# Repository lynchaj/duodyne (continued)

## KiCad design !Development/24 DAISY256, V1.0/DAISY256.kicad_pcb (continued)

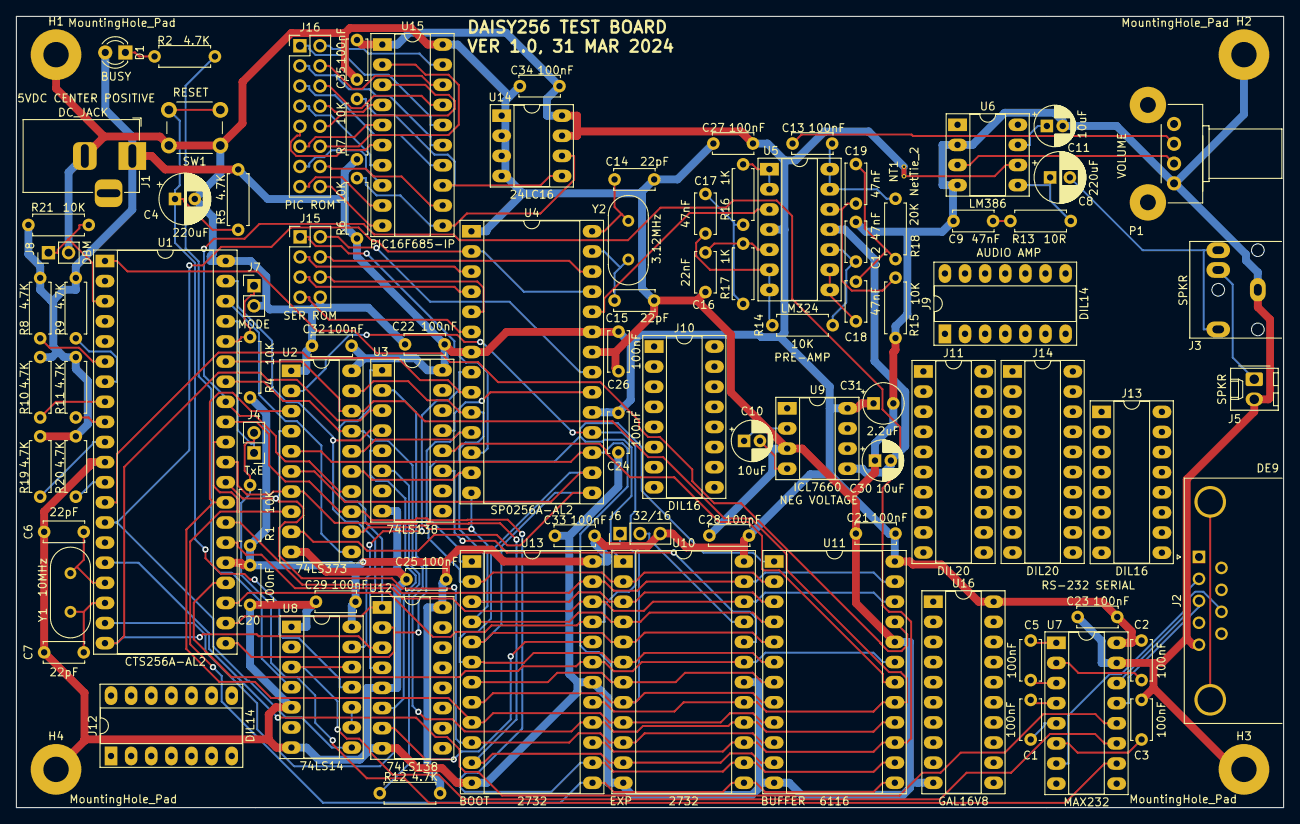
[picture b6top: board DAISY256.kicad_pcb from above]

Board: 2 copper layers, 160.0 x 99.9 mm, 97 parts (0 on the bottom side), 113 nets.

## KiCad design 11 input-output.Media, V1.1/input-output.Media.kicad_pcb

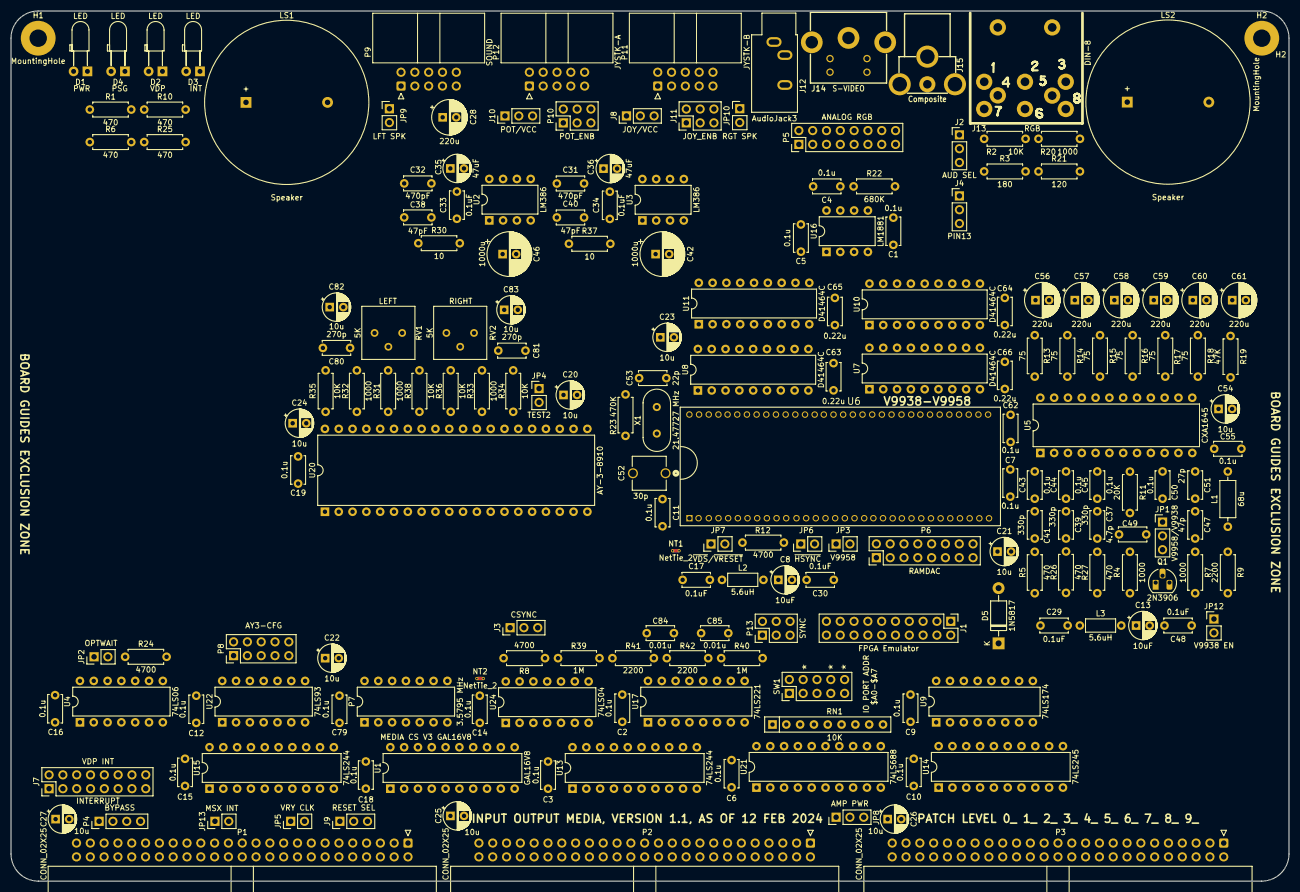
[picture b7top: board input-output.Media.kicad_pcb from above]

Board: 2 copper layers, 235.0 x 160.0 mm, 191 parts (0 on the bottom side), 242 nets, no tracks yet.

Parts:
C1, C2, C3, C4, C5, C6, C7, C9, C10, C11, C12, C14, C15, C16, C18, C19, C43, C44, C45, C50, C55, C62, C79: 0.1u; C_Disc_D5.0mm_W2.5mm_P5.00mm
C8, C13: 10uF; CP_Radial_D5.0mm_P2.50mm
C17, C29, C30, C33, C34, C48: 0.1uF; C_Disc_D5.0mm_W2.5mm_P5.00mm
C20, C21, C22, C23, C24, C25, C26, C27, C54, C82, C83: 10u; CP_Radial_D5.0mm_P2.50mm
C28, C56, C57, C58, C59, C60, C61: 220u; CP_Radial_D6.3mm_P2.50mm
C31, C32: 470pF; C_Disc_D5.0mm_W2.5mm_P5.00mm
C35, C36: 47uF; CP_Radial_D5.0mm_P2.50mm
C37, C39, C41: 330p; C_Disc_D5.0mm_W2.5mm_P5.00mm
C38, C40: 47pF; C_Disc_D5.0mm_W2.5mm_P5.00mm
C42, C46: 1000u; CP_Radial_D8.0mm_P2.50mm
C47: 47p; C_Disc_D5.0mm_W2.5mm_P5.00mm
C49: 4.7p; C_Disc_D5.0mm_W2.5mm_P5.00mm
C51: 27p; C_Disc_D5.0mm_W2.5mm_P5.00mm
C52: 30p; CAP_TZ03R300E169B00_MUR
C53: 22p; C_Disc_D5.0mm_W2.5mm_P5.00mm
C63, C64, C65, C66: 0.22u; C_Disc_D5.0mm_W2.5mm_P5.00mm
C80, C81: 270p; C_Disc_D5.0mm_W2.5mm_P5.00mm
C84, C85: 0.01u; C_Disc_D5.0mm_W2.5mm_P5.00mm
D1, D2, D3, D4: LED; LED_D3.0mm_Horizontal_O3.81mm_Z2.0mm
D5: 1N5817; D_DO-41_SOD81_P10.16mm_Horizontal
H1, H2: MountingHole; MountingHole_3.2mm_M3_Pad
J1: FPGA Emulator; PinHeader_2x10_P2.54mm_Vertical
J2: AUD SEL; PinHeader_1x03_P2.54mm_Vertical
J3: CSYNC; PinHeader_1x03_P2.54mm_Vertical
J4: PIN13; PinHeader_1x03_P2.54mm_Vertical
J7: INTERRUPT; PinHeader_2x08_P2.54mm_Vertical
J8: JOY/VCC; PinHeader_1x03_P2.54mm_Vertical
J9: RESET SEL; PinHeader_1x03_P2.54mm_Vertical
J10: POT/VCC; PinHeader_1x03_P2.54mm_Vertical
J11: JOY_ENB; PinHeader_2x03_P2.54mm_Vertical
J12: AudioJack3; Jack_3.5mm_CUI_SJ1-3533NG_Horizontal
J13: RGB; AV_CON_DIN8
J14: S-VIDEO; Conn_Mini_DIN_4pin
J15: Composite; Conn_RCA_Right
JP1: V9958/V9938; PinHeader_1x03_P2.54mm_Vertical
JP2: OPTWAIT; PinHeader_1x02_P2.54mm_Vertical
JP3: V9958; PinHeader_1x02_P2.54mm_Vertical
JP4: TEST2; PinHeader_1x02_P2.54mm_Vertical
JP5: VRY CLK; PinHeader_1x02_P2.54mm_Vertical
JP6: ~{HSYNC}; PinHeader_1x02_P2.54mm_Vertical
JP7: ~{VDS}/~{VRESET}; PinHeader_1x02_P2.54mm_Vertical
JP8: AMP PWR; PinHeader_1x03_P2.54mm_Vertical
JP9: LFT SPK; PinHeader_1x02_P2.54mm_Vertical
JP10: RGT SPK; PinHeader_1x02_P2.54mm_Vertical
JP12: V9938 EN; PinHeader_1x02_P2.54mm_Vertical
JP13: MSX INT; PinHeader_1x02_P2.54mm_Vertical
L1: 68u; L_Axial_L6.6mm_D2.7mm_P10.16mm_Horizontal_Vishay_IM-2
L2, L3: 5.6uH; L_Axial_L5.3mm_D2.2mm_P7.62mm_Horizontal_Vishay_IM-1
LS1, LS2: Speaker; Jameco PCB Speaker 30mm 135722
NT1, NT2: NetTie_2; NetTie-2_THT_Pad0.3mm
P1, P2, P3: CONN_02X25; IDC-Header_2x25_P2.54mm_Horizontal
P4: BYPASS; PinHeader_1x04_P2.54mm_Vertical
P5: ANALOG RGB; PinHeader_2x08_P2.54mm_Vertical
P6: RAMDAC; PinHeader_2x08_P2.54mm_Vertical
P7: 3.5795 MHz; DIP-14_W7.62mm
P8: AY3-CFG; PinHeader_2x05_P2.54mm_Vertical
P9: SOUND; IDC-Header_2x05_P2.54mm_Horizontal
P10: POT_ENB; PinHeader_2x03_P2.54mm_Vertical
P11: JYSTK-B; IDC-Header_2x05_P2.54mm_Horizontal
P12: JYSTK-A; IDC-Header_2x05_P2.54mm_Horizontal
P13: SYNC; PinHeader_2x03_P2.54mm_Vertical
Q1: 2N3906; TO-92_HandSolder
R1, R5, R6, R10, R25, R26, R27: 470; R_Axial_DIN0207_L6.3mm_D2.5mm_P7.62mm_Horizontal
R2, R34, R35, R36, R38: 10K; R_Axial_DIN0207_L6.3mm_D2.5mm_P7.62mm_Horizontal
R3: 180; R_Axial_DIN0207_L6.3mm_D2.5mm_P7.62mm_Horizontal
R4, R7, R20, R31, R32, R33: 1000; R_Axial_DIN0207_L6.3mm_D2.5mm_P7.62mm_Horizontal
R8, R12, R24: 4700; R_Axial_DIN0207_L6.3mm_D2.5mm_P7.62mm_Horizontal
R9, R41, R42: 2200; R_Axial_DIN0207_L6.3mm_D2.5mm_P7.62mm_Horizontal
R11: 20K; R_Axial_DIN0207_L6.3mm_D2.5mm_P7.62mm_Horizontal
R13, R14, R15, R16, R17, R18: 75; R_Axial_DIN0207_L6.3mm_D2.5mm_P7.62mm_Horizontal
R19: 47K; R_Axial_DIN0207_L6.3mm_D2.5mm_P7.62mm_Horizontal
R21: 120; R_Axial_DIN0207_L6.3mm_D2.5mm_P7.62mm_Horizontal
R22: 680K; R_Axial_DIN0207_L6.3mm_D2.5mm_P7.62mm_Horizontal
R23: 470K; R_Axial_DIN0207_L6.3mm_D2.5mm_P7.62mm_Horizontal
R30, R37: 10; R_Axial_DIN0207_L6.3mm_D2.5mm_P7.62mm_Horizontal
R39, R40: 1M; R_Axial_DIN0207_L6.3mm_D2.5mm_P7.62mm_Horizontal
RN1: 10K; R_Array_SIP9
RV1, RV2: 5K; Potentiometer_Bourns_3386P_Vertical
SW1: IO PORT ADDR; PinHeader_2x05_P2.54mm_Vertical
U1: GAL16V8; DIP-20_W7.62mm
U2, U3: LM386; DIP-8_W7.62mm
U4: 74LS06; DIP-14_W7.62mm
U5: CXA1645; DIP-24_W10.16mm
U6: V9938-V9958; renesas21-DIP64-S
U7, U8, U10, U11: D41464C; DIP-18_W7.62mm
U9: 74LS174; DIP-16_W7.62mm
U13, U15: 74LS244; DIP-20_W7.62mm
U14: 74LS245; DIP-20_W7.62mm
U16: LM1881; DIP-8_W7.62mm
U17: 74LS221; DIP-16_W7.62mm
U20: AY-3-8910; DIP-40_W15.24mm
U21: 74LS688; DIP-20_W7.62mm
U22: 74LS93; DIP-14_W7.62mm
U24: 74LS04; DIP-14_W7.62mm
X1: 21.47727 MHz; Crystal_HC49-4H_Vertical

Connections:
+12V: JP8.3 (B), P2.19, P2.20
-12V: P2.37, P2.38
/ACR/STATUS-PSG: U4.11, U9.10 (Q3)
/ACR/STATUS-VDP: U4.3, U9.7 (Q2)
/Amplifier/AMPPWR: C28.1, C33.2, C34.2, JP8.2 (C), U2.6 (V+), U3.6 (V+)
/Amplifier/R-CH: C42.2, J12.R, JP10.1 (A)
/PSG/CLK_AY3: P7.8, P7.11, P8.6, U22.1 (CP1..3)
/PSG/JOYAD: P12.2, U20.20 (IOA1)
/PSG/JOYAF: P12.6, U20.17 (IOA4)
/PSG/JOYAL: P12.3, U20.19 (IOA2)
/PSG/JOYAR: P12.4, U20.18 (IOA3)
/PSG/JOYAU: P12.1, U20.21 (IOA0)
/PSG/JOYBD: P11.2, U20.12 (IOB1)
/PSG/JOYBF: P11.6, U20.9 (IOB4)
/PSG/JOYBG: J8.3, J11.3, U20.8 (IOB5)
/PSG/JOYBH: J11.1, U20.7 (IOB6)
/PSG/JOYBL: P11.3, U20.11 (IOB2)
/PSG/JOYBR: P11.4, U20.10 (IOB3)
/PSG/JOYBU: P11.1, U20.13 (IOB0)
/PSG/POTA1: J10.3, P10.3, R41.1
/PSG/POTA2: P10.1, R42.1
/PSG/PWA1: U17.13 (Q), U20.16 (IOA5)
/PSG/PWA2: U17.5 (Q), U20.15 (IOA6)
/PSG/SPAREA: P9.4, U20.14 (IOA7)
/PSG/SPAREB: P9.6, U20.6 (IOB7)
/VDP/AD0: U6.49 (AD0), U7.14 (A0), U8.14 (A0), U10.14 (A0), U11.14 (A0)
/VDP/AD1: U6.50 (AD1), U7.13 (A1), U8.13 (A1), U10.13 (A1), U11.13 (A1)
/VDP/AD2: U6.51 (AD2), U7.12 (A2), U8.12 (A2), U10.12 (A2), U11.12 (A2)
/VDP/AD3: U6.52 (AD3), U7.11 (A3), U8.11 (A3), U10.11 (A3), U11.11 (A3)
/VDP/AD4: U6.53 (AD4), U7.8 (A4), U8.8 (A4), U10.8 (A4), U11.8 (A4)
/VDP/AD5: U6.54 (AD5), U7.7 (A5), U8.7 (A5), U10.7 (A5), U11.7 (A5)
/VDP/AD6: U6.55 (AD6), U7.6 (A6), U8.6 (A6), U10.6 (A6), U11.6 (A6)
/VDP/AD7: U6.56 (AD7), U7.10 (A7), U8.10 (A7), U10.10 (A7), U11.10 (A7)
/VDP/AUDIO: J2.2, J13.2
/VDP/AV: J13.3, R2.2, R20.1
/VDP/BLUE: C37.1, C45.1, R27.2, U6.24 (B)
/VDP/BOUT: C58.2, J13.8, P5.3
/VDP/C0: P6.5, U6.19 (C0)
/VDP/C1: P6.6, U6.18 (C1)
/VDP/C2: P6.7, U6.17 (C2)
/VDP/C3: P6.8, U6.16 (C3)
/VDP/C4: P6.9, U6.15 (C4)
/VDP/C5: P6.10, U6.14 (C5)
/VDP/C6: P6.11, U6.13 (C6)
/VDP/C7: P6.12, U6.12 (C7)
/VDP/CBDR: P6.14, U6.11 (CBDR)
/VDP/CHROMA: C61.2, J14.4
/VDP/COMP: C1.1, C59.2, J13.4, J15.1 (In)
/VDP/GOUT: C57.2, J13.7, P5.2
/VDP/GREEN: C39.1, C44.1, R26.2, U6.22 (G)
/VDP/LUMA: C60.2, J14.3
/VDP/RED: C41.1, C43.1, R5.2, U6.23 (R)
/VDP/ROUT: C56.2, J13.6, P5.1
/VDP/SYNCIN: C47.1, J3.3, JP1.2 (C), U5.10 (SYNCIN), U24.13
/VDP/VCCO: D5.1 (K), J1.2
/VDP/VD0: U6.41 (RD0), U7.2 (IO1), U10.2 (IO1)
/VDP/VD1: U6.42 (RD1), U7.3 (IO2), U10.3 (IO2)
/VDP/VD2: U6.43 (RD2), U7.15 (IO3), U10.15 (IO3)
/VDP/VD3: U6.44 (RD3), U7.17 (IO4), U10.17 (IO4)
/VDP/VD4: U6.45 (RD4), U8.2 (IO1), U11.2 (IO1)
/VDP/VD5: U6.46 (RD5), U8.3 (IO2), U11.3 (IO2)
/VDP/VD6: U6.47 (RD6), U8.15 (IO3), U11.15 (IO3)
/VDP/VD7: U6.48 (RD7), U8.17 (IO4), U11.17 (IO4)
/VDP/VGA-CSYNC: J3.2, J4.3, P5.16
/VDP/VGA-HSYNC: J4.1, P13.3
/VDP/VGA-VSYNC: P5.14, P13.4
/VDP/VSYNC: P13.2, U16.3 (FRAME), U24.3
/VDP/YS: J13.5, R3.2, R21.1
/VDP/~CAS0: U6.61 (~CAS0), U7.16 (CAS), U8.16 (CAS)
/VDP/~CAS1: U6.60 (~CAS1), U10.16 (CAS), U11.16 (CAS)
/VDP/~CSYNC: R4.2, U6.6 (~CSYNC)
/VDP/~DHCLK: P6.3, U6.2 (~DHCLK)
/VDP/~DLCLK: P6.4, R12.1, U6.3 (~DLCLK)
/VDP/~HSYNC: JP6.1 (A), P13.5, U6.5 (~HSYNC), U24.1
/VDP/~RAS: U6.62 (~RAS), U7.5 (RAS), U8.5 (RAS), U10.5 (RAS), U11.5 (RAS)
/VDP/~VRW: U6.57 (R/~W), U7.4 (WE), U8.4 (WE), U10.4 (WE), U11.4 (WE)
/VDP/~VSYNC: P13.6, U24.4
A0: P2.35, U13.2 (I0a)
A1: P2.33, U13.4 (I1a)
A2: P2.31, U13.6 (I2a)
A3: P2.29, U13.8 (I3a)
A4: P2.27, U13.11 (I0b)
A5: P2.25, U13.13 (I1b)
A6: P2.23, U13.15 (I2b)
A7: P2.21, U13.17 (I3b)
ACR5: P9.8, U9.15 (Q5)
AUDIO_L: C32.1, C82.2, P9.3, U2.3 (+)
AUDIO_R: C31.1, C83.2, P9.9, U3.3 (+)
CLK: JP5.2 (B), P1.15
D0: P3.33, U14.2 (A0)
D1: P3.31, U14.3 (A1)
D2: P3.29, U14.4 (A2)
D3: P3.27, U14.5 (A3)
D4: P3.25, U14.6 (A4)
D5: P3.23, U14.7 (A5)
D6: P3.21, U14.8 (A6)
D7: P3.19, U14.9 (A7)
GND: C2.2, C3.2, C4.2, C5.2, C6.2, C7.2, C8.2, C9.2, C10.2, C11.2, C12.2, C13.2, C14.2, C15.2, C16.2, C17.2, C18.2, C19.2, C20.2, C21.2, C22.2, C23.2, C24.2, C25.2, C26.2, C27.2, C28.2, C29.2, C30.2, C31.2, C32.2, C33.1, C34.1, C35.2, C36.2, C37.2, C38.2, C39.2, C40.2, C41.2, C47.2, C48.2, C49.2, C50.2, C52.2, C53.2, C54.2, C55.2, C62.2, C63.2, C64.2, C65.2, C66.2, C79.2, C80.1, C81.2, D1.1 (K), H1.1, H2.1, J1.1, J1.3, J2.3, J12.S, J13.1, J14.1, J14.2, J15.2 (Ext), JP4.1 (A), L1.2, LS1.2, LS2.2, NT2.1, P1.49, P1.50, P2.49, P2.50, P3.49, P3.50, P5.5, P5.6, P5.7, P5.8, P5.10, P6.1, P6.16, P7.4, P7.7, P9.5, P9.7, P9.10, P11.8, P12.8, R2.1, R3.1, R5.1, R7.1, R11.2, R19.2, R22.2, R26.1, R27.1, R31.2, R32.2, R33.2, RV1.1, RV2.1, U1.10 (GND), U2.2 (-), U2.4 (GND), U3.2 (-), U3.4 (GND), U4.7 (GND), U5.1 (GND), U5.24 (GND), U6.1 (GND), U6.20 (GND), U7.18 (GND), U8.18 (GND), U9.8 (GND), U10.18 (GND), U11.18 (GND), U13.10 (GND), U14.10 (GND), U15.10 (GND), U16.4 (GND), U17.8 (GND), U20.1 (GND), U21.10 (GND), U22.10 (GND), U24.7 (GND)
L-CH: C46.2, J2.1, J12.T, JP9.1 (A)
unnamed: C1.2, U16.2 (VIDEO)
unnamed: C4.1, R22.1, U16.6 (INT)
unnamed: C35.1, U2.7 (BYPASS)
unnamed: C36.1, U3.7 (BYPASS)
unnamed: C38.1, R30.1
unnamed: C40.1, R37.1
unnamed: C42.1, R37.2, U3.5
unnamed: C43.2, U5.2 (RIN)
unnamed: C44.2, U5.3 (GIN)
unnamed: C45.2, U5.4 (BIN)
unnamed: C46.1, R30.2, U2.5
unnamed: C49.1, R9.1, U5.6 (SCIN)
unnamed: C50.1, U5.9 (YCLPC)
unnamed: C51.1, U5.17 (YTRAP)
unnamed: C51.2, L1.1
unnamed: C52.1, R23.2, U6.63 (XTAL1), X1.1
unnamed: C53.1, R23.1, U6.64 (XTAL2), X1.2
unnamed: C54.1, U5.14 (VREF)
unnamed: C55.1, R19.1, U5.13 (IREF)
unnamed: C56.1, R13.1
unnamed: C57.1, R14.1
unnamed: C58.1, R15.1
unnamed: C59.1, R16.1
unnamed: C60.1, R17.1
unnamed: C61.1, R18.1
unnamed: C62.1, U6.33 (VBB)
unnamed: C80.2, C82.1, R34.1, R36.2, RV1.2, RV1.3
unnamed: C81.1, C83.1, R35.1, R38.2, RV2.2, RV2.3
unnamed: C84.1, U17.15 (RCext)
unnamed: C84.2, R39.2, R41.2, U17.14 (Cext)
unnamed: C85.1, U17.7 (RCext)
unnamed: C85.2, R40.2, R42.2, U17.6 (Cext)
unnamed: D1.2 (A), R1.1
unnamed: D2.1 (K), U4.4
unnamed: D2.2 (A), R6.1
unnamed: D3.2 (A), R25.1
unnamed: D4.1 (K), U4.10
unnamed: D4.2 (A), R10.1
unnamed: J3.1, U24.12
unnamed: J4.2, P5.13
unnamed: J7.1, J7.3, J7.5, J7.7, J7.9, J7.11, J7.13, J7.15, JP13.1 (A), U4.6
unnamed: J8.2, P11.9
unnamed: J9.2, U15.2 (I0a)
unnamed: J10.2, P12.9
unnamed: J11.2, P11.5
unnamed: J11.4, P11.7
unnamed: J11.6, P11.10
unnamed: JP1.1 (A), U24.10
unnamed: JP1.3 (B), JP12.1 (A), R4.1
unnamed: JP2.1 (A), U4.2
unnamed: JP3.1 (A), U6.21 (COMPVID/DACVCC)
unnamed: JP4.2 (B), U20.26 (TEST2)
unnamed: JP7.1 (A), U6.4 (~VDS/~VRESET)
unnamed: JP9.2 (B), LS1.1
unnamed: JP10.2 (B), LS2.1
unnamed: JP12.2 (B), Q1.2 (B)
unnamed: P8.1, P8.3, R31.1, R36.1, R38.1, U20.3 (OUTB)
unnamed: P8.2, R32.1, R35.2, U20.38 (OUTC)
unnamed: P8.4, R33.1, R34.2, U20.4 (OUTA)
unnamed: P8.5, U22.9 (Q1)
unnamed: P8.7, P8.8, U20.22 (CLOCK)
unnamed: P8.9, U22.11 (Q3)
unnamed: P8.10, U22.8 (Q2)
unnamed: P10.2, P12.5
unnamed: P10.4, P12.7
unnamed: P10.6, P12.10
unnamed: P13.1, U24.2
unnamed: Q1.3 (C), R7.2, U24.11
unnamed: R11.1, U5.18 (FO)
unnamed: R13.2, U5.23 (ROUT)
unnamed: R14.2, U5.22 (GOUT)
unnamed: R15.2, U5.21 (BOUT)
unnamed: R16.2, U5.20 (CVOUT)
unnamed: R17.2, U5.16 (YOUT)
unnamed: R18.2, U5.15 (COUT)
unnamed: R24.1, U4.5, U4.8
unnamed: RN1.2 (R1), SW1.1, U21.18 (R7)
unnamed: RN1.3 (R2), SW1.3, U21.16 (R6)
unnamed: RN1.4 (R3), SW1.5, U21.14 (R5)
unnamed: RN1.5 (R4), SW1.7, U21.12 (R4)
unnamed: RN1.6 (R5), SW1.9, U21.9 (R3)
unnamed: RN1.9 (R8), U21.3 (R0), U21.4 (P1), U21.5 (R1), U21.6 (P2), U21.7 (R2)
unnamed: U9.2 (Q0), U24.5
unnamed: U4.1, U24.8
ONE: JP7.2 (B), NT1.2, U6.27 (~LPD/~HRESET), U17.2 (B), U17.3 (~CLR), U17.10 (B), U17.11 (~CLR), U20.25 (A8), U20.28 (BC2)
VCC: C2.1, C3.1, C5.1, C6.1, C7.1, C9.1, C10.1, C11.1, C12.1, C14.1, C15.1, C16.1, C18.1, C19.1, C20.1, C21.1, C22.1, C23.1, C24.1, C25.1, C26.1, C27.1, C63.1, C64.1, C65.1, C66.1, C79.1, D5.2 (A), J8.1, J10.1, J11.5, JP3.2 (B), JP8.1 (A), L2.1, L3.1, NT1.1, P1.1, P1.2, P2.1, P2.2, P3.1, P3.2, P5.9, P6.2, P6.15, P7.14, P9.1, P9.2, P10.5, Q1.1 (E), R1.2, R6.2, R8.2, R10.2, R12.2, R20.2, R21.2, R24.2, R25.2, R39.1, R40.1, RN1.1 (common), U1.20 (VCC), U4.14 (VCC), U5.7 (NTSC/~PAL), U7.9 (VCC), U8.9 (VCC), U9.16 (VCC), U10.9 (VCC), U11.9 (VCC), U13.20 (VCC), U14.20 (VCC), U15.20 (VCC), U16.8 (VCC), U17.16 (VCC), U20.40 (VCC), U21.20 (VCC), U22.5 (VCC), U24.14 (VCC)
VCCRGB: C13.1, C29.1, C48.1, L3.2, U5.12 (VCC), U5.19 (VCC)
VCCVDP: C8.1, C17.1, C30.1, L2.2, U6.58 (VCC)
VRY: J1.4, U6.8 (CPUCLK/~VDS), U15.4 (I1a)
VRY_CLK: JP5.1 (A), R9.2, U15.16 (O1a)
ZERO: JP6.2 (B), NT2.2, SW1.2, SW1.4, SW1.6, SW1.8, SW1.10, U7.1 (OE), U8.1 (OE), U10.1 (OE), U11.1 (OE), U13.1 (OEa), U13.19 (OEb), U15.1 (OEa), U15.19 (OEb), U20.24 (A9), U22.2 (R0(1)), U22.3 (R0(2)), U22.14 (CP0)
bA0: J1.14, U1.6 (I6), U6.29 (MODE0), U13.18 (O0a)
bA1: J1.10, U1.7 (I7), U6.28 (MODE1), U13.16 (O1a)
bA2: U1.5 (I5), U13.14 (O2a)
bA3: U13.12 (O3a), U21.8 (P3)
bA4: U13.9 (O0b), U21.11 (P4)
bA5: U13.7 (O1b), U21.13 (P5)
bA6: U13.5 (O2b), U21.15 (P6)
bA7: U13.3 (O3b), U21.17 (P7)
bD0: J1.19, U6.40 (CD0), U9.3 (D0), U14.18 (B0), U20.37 (D0)
bD1: J1.17, U6.39 (CD1), U9.4 (D1), U14.17 (B1), U20.36 (D1)
bD2: J1.15, U6.38 (CD2), U9.6 (D2), U14.16 (B2), U20.35 (D2)
bD3: J1.13, U6.37 (CD3), U9.11 (D3), U14.15 (B3), U20.34 (D3)
bD4: J1.11, U6.36 (CD4), U9.13 (D4), U14.14 (B4), U20.33 (D4)
bD5: J1.9, U6.35 (CD5), U9.14 (D5), U14.13 (B5), U20.32 (D5)
bD6: J1.7, U6.34 (CD6), U14.12 (B6), U20.31 (D6)
bD7: J1.5, U6.32 (CD7), U14.11 (B7), U20.30 (D7)
~BAI: P1.40, P4.4
~BAO: P1.42, P4.3
~CS_ACR_WR: U1.15 (IO5), U9.9 (Cp)
~CS_ACR: U1.14 (IO6), U17.1 (~A), U17.9 (~A)
~CS_MEDIA: U1.3 (I3), U14.19 (CE), U21.19 (P=R)
~CS_PSG_A0: U1.16 (IO4), U20.29 (BC1)
~CS_PSG_WR: U1.17 (I03), U20.27 (BDIR)
~EIRQ0: J7.2, P1.45
~EIRQ1: J7.4, P1.43
~EIRQ2: J7.6, P1.41
~EIRQ3: J7.8, P1.39
~EIRQ4: J7.10, P1.37
~EIRQ5: J7.12, P1.35
~EIRQ6: J7.14, P1.33
~EIRQ7: J7.16, P1.31
~IEI: P1.44, P4.2
~IEO: P1.46, P4.1
~INT0: JP13.2 (B), P1.17
~IORQ: P1.7, U15.11 (I0b)
~LPS-WAIT: J1.6, R8.1, U6.26 (~LPS/~WAIT), U24.9
~M1: P1.11, U15.13 (I1b)
~RD: P1.3, U14.1 (A->B), U15.17 (I3b)
~RESAY3: U9.12 (Q4), U20.23 (RESET)
~RESVDP: J1.12, U6.9 (~RESET), U24.6
~RES_IN: J9.1, P1.20
~RES_OUT: J9.3, P1.21
~VDP_RD: J1.18, U1.18 (IO2), U6.31 (~CSR)
~VDP_WR: J1.16, U1.19 (IO1), U6.30 (~CSW)
~VINT: D3.1 (K), J1.20, U4.9, U6.25 (~INT)
~WAIT: JP2.2 (B), P1.25
~WR: P1.5, U15.15 (I2b)
~bIORQ: U15.9 (O0b), U21.1 (G)
~bM1: U15.7 (O1b), U21.2 (P0)
~bRD: U1.4 (I4), U15.3 (O3b)
~bRESET: U9.1 (~Mr), U15.18 (O0a)
~bWR: U1.2 (I2), U15.5 (O2b)

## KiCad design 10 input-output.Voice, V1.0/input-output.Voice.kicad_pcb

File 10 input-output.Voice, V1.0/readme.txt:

The input-output.Voice board is a specialized audio board for speech.  It contains a CTS256A-AL2 and SP0256A-AL2 text to speech (TTS) chipset, a DAC and ADC for audio frequencies, and left and right channel sound synthesis (SN76489N) chips.  There is a mixer combining all four sources of audio to output to either onboard speakers and/or headphone jack.  Also includes a microphone jack for ADC recording voice audio.

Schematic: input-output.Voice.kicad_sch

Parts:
H3, H4: MountingHole; MountingHole_2.2mm_M2_DIN965_Pad
J1, J4: DIL14; DIP-14_W7.62mm_Socket
J2, J5: DIL16; DIP-16_W7.62mm_Socket
J3, J6: DIL20; DIP-20_W7.62mm_Socket
U19: GAL16V8; DIP-20_W7.62mm_Socket

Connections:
GND: U19.10 (GND); also elsewhere on the board
VCC: U19.20 (VCC); also elsewhere on the board

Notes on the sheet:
SPARE SOCKETS FOR DEBUGGING
SPARE GAL FOR DEBUGGING
THROUGH HOLES FOR PATCH WIRE ROUTING ACROSS SIDES

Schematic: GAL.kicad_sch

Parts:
U1: GAL16V8; DIP-20_W7.62mm_Socket

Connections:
A15-TTS: U1.7 (I7); also elsewhere on the board
CS_TTS: U1.14 (IO6); also elsewhere on the board
GND: U1.10 (GND); also elsewhere on the board
VCC: U1.20 (VCC); also elsewhere on the board
bA0: U1.4 (I4); also elsewhere on the board
bA1: U1.3 (I3); also elsewhere on the board
bA2: U1.5 (I5); also elsewhere on the board
~A15: U1.12 (IO8); also elsewhere on the board
~BRD_SEL: U1.2 (I2); also elsewhere on the board
~CS_ADC_WR: U1.13 (IO7); also elsewhere on the board
~CS_ADC: U1.18 (IO2); also elsewhere on the board
~CS_DAC_WR: U1.17 (I03); also elsewhere on the board
~CS_SN1: U1.16 (IO4); also elsewhere on the board
~CS_SN2: U1.15 (IO5); also elsewhere on the board
~CS_TTS: U1.19 (IO1); also elsewhere on the board
~bWR: U1.6 (I6); also elsewhere on the board

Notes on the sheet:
VOICE CS V3 GAL16V8

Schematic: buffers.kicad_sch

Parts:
J11: RESET SEL; PinHeader_1x03_P2.54mm_Vertical
U20, U22: 74LS244; DIP-20_W7.62mm_Socket
U21: 74LS245; DIP-20_W7.62mm_Socket

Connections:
A0: U20.2 (I0a); also elsewhere on the board
A1: U20.4 (I1a); also elsewhere on the board
A2: U20.6 (I2a); also elsewhere on the board
A3: U20.8 (I3a); also elsewhere on the board
A4: U20.11 (I0b); also elsewhere on the board
A5: U20.13 (I1b); also elsewhere on the board
A6: U20.15 (I2b); also elsewhere on the board
A7: U20.17 (I3b); also elsewhere on the board
D0: U21.2 (A0); also elsewhere on the board
D1: U21.3 (A1); also elsewhere on the board
D2: U21.4 (A2); also elsewhere on the board
D3: U21.5 (A3); also elsewhere on the board
D4: U21.6 (A4); also elsewhere on the board
D5: U21.7 (A5); also elsewhere on the board
D6: U21.8 (A6); also elsewhere on the board
D7: U21.9 (A7); also elsewhere on the board
GND: U20.10 (GND), U21.10 (GND), U22.10 (GND); also elsewhere on the board
unnamed: J11.2, U22.2 (I0a)
VCC: U20.20 (VCC), U21.20 (VCC), U22.20 (VCC); also elsewhere on the board
ZERO: U20.1 (OEa), U20.19 (OEb), U22.1 (OEa), U22.19 (OEb); also elsewhere on the board
bA0: U20.18 (O0a); also elsewhere on the board
bA1: U20.16 (O1a); also elsewhere on the board
bA2: U20.14 (O2a); also elsewhere on the board
bA3: U20.12 (O3a); also elsewhere on the board
bA4: U20.9 (O0b); also elsewhere on the board
bA5: U20.7 (O1b); also elsewhere on the board
bA6: U20.5 (O2b); also elsewhere on the board
bA7: U20.3 (O3b); also elsewhere on the board
bD0: U21.18 (B0); also elsewhere on the board
bD1: U21.17 (B1); also elsewhere on the board
bD2: U21.16 (B2); also elsewhere on the board
bD3: U21.15 (B3); also elsewhere on the board
bD4: U21.14 (B4); also elsewhere on the board
bD5: U21.13 (B5); also elsewhere on the board
bD6: U21.12 (B6); also elsewhere on the board
bD7: U21.11 (B7); also elsewhere on the board
~CS_TTS: U21.19 (CE); also elsewhere on the board
~IORQ: U22.11 (I0b); also elsewhere on the board
~M1: U22.13 (I1b); also elsewhere on the board
~RD: U21.1 (A->B), U22.17 (I3b); also elsewhere on the board
~RES_IN: J11.1; also elsewhere on the board
~RES_OUT: J11.3; also elsewhere on the board
~WR: U22.15 (I2b); also elsewhere on the board
~bIORQ: U22.9 (O0b); also elsewhere on the board
~bM1: U22.7 (O1b); also elsewhere on the board
~bRD: U22.3 (O3b); also elsewhere on the board
~bRESET: U22.18 (O0a); also elsewhere on the board
~bWR: U22.5 (O2b); also elsewhere on the board

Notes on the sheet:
Z80 BUS INTERFACE
Note: Buffers and Transceivers respond to IO and MEM cycles

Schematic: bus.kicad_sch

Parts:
P1, P2, P3: CONN_02X25; IDC-Header_2x25_P2.54mm_Horizontal
P4: BYPASS; PinHeader_1x04_P2.54mm_Vertical

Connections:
+12V: P2.19, P2.20; also elsewhere on the board
-12V: P2.37, P2.38; also elsewhere on the board
/bus/A8: P2.17
/bus/A9: P2.15
/bus/A10: P2.13
/bus/A11: P2.11
/bus/A12: P2.9
/bus/A13: P2.7
/bus/A14: P2.5
/bus/A15: P2.3
/bus/A16: P2.36
/bus/A17: P2.34
/bus/A18: P2.32
/bus/A19: P2.30
/bus/A20: P2.28
/bus/A21: P2.26
/bus/A22: P2.24
/bus/A23: P2.22
/bus/A24: P2.18
/bus/A25: P2.16
/bus/A26: P2.14
/bus/A27: P2.12
/bus/A28: P2.10
/bus/A29: P2.8
/bus/A30: P2.6
/bus/A31: P2.4
/bus/AUXCLK0: P2.48
/bus/AUXCLK1: P2.47
/bus/AUXCLK2: P3.48
/bus/AUXCLK3: P3.46
/bus/CLK: P1.15
/bus/CRUCLK: P1.14
/bus/CRUIN: P1.18
/bus/CRUOUT: P1.16
/bus/D8: P3.17
/bus/D9: P3.15
/bus/D10: P3.13
/bus/D11: P3.11
/bus/D12: P3.9
/bus/D13: P3.7
/bus/D14: P3.5
/bus/D15: P3.3
/bus/D16: P3.34
/bus/D17: P3.32
/bus/D18: P3.30
/bus/D19: P3.28
/bus/D20: P3.26
/bus/D21: P3.24
/bus/D22: P3.22
/bus/D23: P3.20
/bus/D24: P3.18
/bus/D25: P3.16
/bus/D26: P3.14
/bus/D27: P3.12
/bus/D28: P3.10
/bus/D29: P3.8
/bus/D30: P3.6
/bus/D31: P3.4
/bus/E: P1.4
/bus/I2C_SCL: P1.47
/bus/I2C_SDA: P1.48
/bus/IC0: P2.45
/bus/IC1: P2.43
/bus/IC2: P2.41
/bus/IC3: P2.39
/bus/IPL0: P3.47
/bus/IPL1: P3.45
/bus/IPL2: P3.43
/bus/LDS: P3.38
/bus/PHI: P1.8
/bus/S0: P3.44
/bus/S1: P3.42
/bus/S2: P3.40
/bus/ST: P1.6
/bus/UDS: P3.36
/bus/USER0: P1.38
/bus/USER1: P1.36
/bus/USER2: P1.34
/bus/USER3: P1.32
/bus/USER4: P1.30
/bus/USER5: P1.28
/bus/USER6: P1.26
/bus/USER7: P1.24
/bus/USER8: P1.22
/bus/~BHE: P3.41
/bus/~BUSACK: P1.13
/bus/~BUSERR: P3.35
/bus/~BUSRQ: P1.23
/bus/~DREQ0: P2.46
/bus/~DREQ1: P2.42
/bus/~HALT: P1.27
/bus/~INT0: P1.17
/bus/~INT1: P1.12
/bus/~INT2: P1.10
/bus/~MREQ: P1.9
/bus/~NMI: P1.19
/bus/~RFSH: P1.29
/bus/~TEND0: P2.44
/bus/~TEND1: P2.40
/bus/~VMA: P3.39
/bus/~VPA: P3.37
A0: P2.35; also elsewhere on the board
A1: P2.33; also elsewhere on the board
A2: P2.31; also elsewhere on the board
A3: P2.29; also elsewhere on the board
A4: P2.27; also elsewhere on the board
A5: P2.25; also elsewhere on the board
A6: P2.23; also elsewhere on the board
A7: P2.21; also elsewhere on the board
D0: P3.33; also elsewhere on the board
D1: P3.31; also elsewhere on the board
D2: P3.29; also elsewhere on the board
D3: P3.27; also elsewhere on the board
D4: P3.25; also elsewhere on the board
D5: P3.23; also elsewhere on the board
D6: P3.21; also elsewhere on the board
D7: P3.19; also elsewhere on the board
GND: P1.49, P1.50, P2.49, P2.50, P3.49, P3.50; also elsewhere on the board
VCC: P1.1, P1.2, P2.1, P2.2, P3.1, P3.2; also elsewhere on the board
~BAI: P1.40, P4.4
~BAO: P1.42, P4.3
~EIRQ0: P1.45; also elsewhere on the board
~EIRQ1: P1.43; also elsewhere on the board
~EIRQ2: P1.41; also elsewhere on the board
~EIRQ3: P1.39; also elsewhere on the board
~EIRQ4: P1.37; also elsewhere on the board
~EIRQ5: P1.35; also elsewhere on the board
~EIRQ6: P1.33; also elsewhere on the board
~EIRQ7: P1.31; also elsewhere on the board
~IEI: P1.44, P4.2
~IEO: P1.46, P4.1
~IORQ: P1.7; also elsewhere on the board
~M1: P1.11; also elsewhere on the board
~RD: P1.3; also elsewhere on the board
~RES_IN: P1.20; also elsewhere on the board
~RES_OUT: P1.21; also elsewhere on the board
~WAIT: P1.25; also elsewhere on the board
~WR: P1.5; also elsewhere on the board

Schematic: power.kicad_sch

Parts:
C1, C2, C3, C4, C5, C6, C7, C8, C9, C10, C11, C12, C13, C14, C15, C16, C17, C18, C19: 0.1u; C_Disc_D5.0mm_W2.5mm_P5.00mm
C20, C21, C22, C23, C24, C25, C26, C27: 10u; CP_Radial_D5.0mm_P2.50mm
D1: LED; LED_D3.0mm_Horizontal_O3.81mm_Z2.0mm
H1, H2: MountingHole; MountingHole_3.2mm_M3_Pad
JP9: SPR1; PinHeader_1x02_P2.54mm_Vertical
JP10: SPR2; PinHeader_1x02_P2.54mm_Vertical
NT1, NT2: NetTie_2; NetTie-2_THT_Pad0.3mm
R1: 470; R_Axial_DIN0207_L6.3mm_D2.5mm_P7.62mm_Horizontal
U12: 74LS06; DIP-14_W7.62mm_Socket
U27, U28: LM324; DIP-14_W7.62mm_Socket

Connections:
GND: C1.2, C2.2, C3.2, C4.2, C5.2, C6.2, C7.2, C8.2, C9.2, C10.2, C11.2, C12.2, C13.2, C14.2, C15.2, C16.2, C17.2, C18.2, C19.2, C20.2, C21.2, C22.2, C23.2, C24.2, C25.2, C26.2, C27.2, D1.1 (K), H1.1, H2.1, JP9.1 (A), JP10.1 (A), NT2.1, U12.7 (GND); also elsewhere on the board
unnamed: D1.2 (A), R1.1
unnamed: JP9.2 (B), U27.13 (-)
unnamed: JP10.2 (B), U28.13 (-)
ONE: NT1.2; also elsewhere on the board
VB: U27.12 (+), U28.12 (+); also elsewhere on the board
VCC: C1.1, C2.1, C3.1, C4.1, C5.1, C6.1, C7.1, C8.1, C9.1, C10.1, C11.1, C12.1, C13.1, C14.1, C15.1, C16.1, C17.1, C18.1, C19.1, C20.1, C21.1, C22.1, C23.1, C24.1, C25.1, C26.1, C27.1, NT1.1, R1.2, U12.14 (VCC); also elsewhere on the board
ZERO: NT2.2; also elsewhere on the board

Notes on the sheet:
Spare Components

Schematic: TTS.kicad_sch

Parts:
C37, C38, C39, C40: 22p; C_Disc_D3.0mm_W1.6mm_P2.50mm
D2: LED; LED_D3.0mm_Horizontal_O3.81mm_Z2.0mm
J7: TTL TTS SER; PinHeader_1x06_P2.54mm_Vertical
J8: 2716 2732; PinHeader_1x03_P2.54mm_Vertical
JP1: SER PWR; PinHeader_1x02_P2.54mm_Vertical
JP2: TXD EN; PinHeader_1x02_P2.54mm_Vertical
NT3, NT4: NetTie_2; NetTie-2_THT_Pad0.3mm
R7: 10K; R_Axial_DIN0207_L6.3mm_D2.5mm_P7.62mm_Horizontal
R8: 470; R_Axial_DIN0207_L6.3mm_D2.5mm_P7.62mm_Horizontal
R42: 2200; R_Axial_DIN0207_L6.3mm_D2.5mm_P7.62mm_Horizontal
RN1: 10K; R_Array_SIP9
RN2: 470; R_Array_SIP9
SW1: INP OPTS; PinHeader_2x06_P2.54mm_Vertical
SW2: UART PARM; PinHeader_2x08_P2.54mm_Vertical
U2: 74LS374; DIP-20_W7.62mm_Socket
U3: CTS256A-AL2; DIP-40_W15.24mm_Socket
U4: 6116; DIP-24_W15.24mm_Socket
U5, U9: 74LS373; DIP-20_W7.62mm_Socket
U6: 74LS138; DIP-16_W7.62mm_Socket
U7: 2732; DIP-24_W15.24mm_Socket
U8: SP0256A-AL2; DIP-28_W15.24mm_Socket
U12: 74LS06; DIP-14_W7.62mm_Socket
Y1: 10 MHz; Crystal_HC49-4H_Vertical
Y2: 3.12 MHz; Crystal_HC49-4H_Vertical

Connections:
/TTS/A0: U4.8 (A0), U5.2 (O0), U7.8 (A0), U8.18 (A1)
/TTS/A1: U4.7 (A1), U5.5 (O1), U7.7 (A1), U8.17 (A2)
/TTS/A2: U4.6 (A2), U5.6 (O2), U7.6 (A2), U8.16 (A3)
/TTS/A3: U4.5 (A3), U5.9 (O3), U7.5 (A3), U8.15 (A4)
/TTS/A4: U4.4 (A4), U5.12 (O4), U7.4 (A4), U8.14 (A5)
/TTS/A5: U4.3 (A5), U5.15 (O5), U7.3 (A5), U8.13 (A6)
/TTS/A6: U4.2 (A6), U5.16 (O6), U7.2 (A6), U8.11 (A7)
/TTS/A7: U4.1 (A7), U5.19 (O7), U7.1 (A7), U8.10 (A8)
/TTS/A8: U3.27 (A8), U4.23 (A8), U7.23 (A8)
/TTS/A9: U3.26 (A9), U4.22 (A9), U7.22 (A9)
/TTS/A10: U3.24 (A10), U4.19 (A10), U7.19 (A10)
/TTS/A11: J8.1, U3.23 (A11)
/TTS/A12: U3.22 (A12), U6.1 (A0)
/TTS/A13: U3.21 (A13), U6.2 (A1)
/TTS/A14: U3.20 (A14), U6.3 (A2)
/TTS/BUSY: R42.2, U12.10, U12.13
/TTS/D0: U2.2 (O0), U3.28 (D0), U4.9 (Q0), U5.3 (D0), U7.9 (Q0), U9.19 (O7)
/TTS/D1: U2.5 (O1), U3.29 (D1), U4.10 (Q1), U5.4 (D1), U7.10 (Q1), U9.16 (O6)
/TTS/D2: U2.6 (O2), U3.30 (D2), U4.11 (Q2), U5.7 (D2), U7.11 (Q2), U9.15 (O5)
/TTS/D3: U2.9 (O3), U3.31 (D3), U4.13 (Q3), U5.8 (D3), U7.13 (Q3), U9.12 (O4)
/TTS/D4: U2.12 (O4), U3.32 (D4), U4.14 (Q4), U5.13 (D4), U7.14 (Q4), U9.9 (O3)
/TTS/D5: U2.15 (O5), U3.33 (D5), U4.15 (Q5), U5.14 (D5), U7.15 (Q5), U9.6 (O2)
/TTS/D6: U2.16 (O6), U3.34 (D6), U4.16 (Q6), U5.17 (D6), U7.16 (Q6), U9.5 (O1)
/TTS/D7: U2.19 (O7), U3.35 (D7), U4.17 (Q7), U5.18 (D7), U7.17 (Q7), U9.2 (O0)
/TTS/LE: U3.38 (ALATCH), U5.11 (LE)
/TTS/RXD: J7.4, U3.16 (RXD)
/TTS/SBY: U8.8 (SBY), U12.11
/TTS/TXD: J7.5, JP2.1 (A), R7.2
/TTS/~ALD: U6.13 (O2), U8.20 (~ALD)
/TTS/~BUSY: J7.2, U3.3 (~BUSY)
/TTS/~CS_RAM: U4.18 (~CS), U6.12 (O3)
/TTS/~CS_ROM: U6.11 (O4), U7.20 (~G)
/TTS/~ENABLE: U3.39 (~ENABLE), U6.4 (E1)
/TTS/~LOE: U2.1 (OE), U6.15 (O0)
/TTS/~LRQ: U3.13 (~INT1), U8.9 (~LRQ)
/TTS/~UART_PAR: U6.14 (O1), U9.1 (OE)
/TTS/~WE: U3.1 (~R/W), U4.21 (~WE)
A15-TTS: U3.19 (A15); also elsewhere on the board
AUDIO_TTS: U8.24 (OUT); also elsewhere on the board
CS_TTS: U2.11 (Cp); also elsewhere on the board
GND: C37.2, C38.2, C39.2, C40.2, J7.1, NT4.1, RN1.1 (common), RN2.1 (common), U2.10 (GND), U4.12 (GND), U5.10 (GND), U6.8 (GND), U7.12 (GND), U9.10 (GND); also elsewhere on the board
unnamed: C37.1, U3.17 (X2), Y1.1
unnamed: C38.1, U3.18 (X1), Y1.2
unnamed: C39.1, U8.27 (OSC1), Y2.1
unnamed: C40.1, U8.28 (OSC2), Y2.2
unnamed: D2.1 (K), U12.12
unnamed: D2.2 (A), R8.2
unnamed: J7.3, JP1.1 (A)
unnamed: J8.2, U7.21 (A11)
unnamed: JP2.2 (B), U3.37 (TXD)
unnamed: RN1.2 (R1), SW1.2, U3.6 (OPT6)
unnamed: RN1.3 (R2), SW1.4, U3.7 (OPT7)
unnamed: RN1.4 (R3), SW1.6, U3.8 (OPT8)
unnamed: RN1.5 (R4), SW1.8, U3.9 (OPT9)
unnamed: RN1.6 (R5), SW1.10, U3.10 (OPT10)
unnamed: RN1.7 (R6), SW1.12, U3.11 (OPT11)
unnamed: RN2.2 (R1), SW2.2, U9.3 (D0)
unnamed: RN2.3 (R2), SW2.4, U9.4 (D1)
unnamed: RN2.4 (R3), SW2.6, U9.7 (D2)
unnamed: RN2.5 (R4), SW2.8, U9.8 (D3)
unnamed: RN2.6 (R5), SW2.10, U9.13 (D4)
unnamed: RN2.7 (R6), SW2.12, U9.14 (D5)
unnamed: RN2.8 (R7), SW2.14, U9.17 (D6)
unnamed: RN2.9 (R8), SW2.16, U9.18 (D7)
ONE: J8.3, SW1.1, SW1.3, SW1.5, SW1.7, SW1.9, SW1.11, SW2.1, SW2.3, SW2.5, SW2.7, SW2.9, SW2.11, SW2.13, SW2.15, U8.19 (SE), U8.23 (VD1); also elsewhere on the board
VCC: JP1.2 (B), NT3.1, R7.1, R8.1, R42.1, U2.20 (VCC), U4.24 (VCC), U5.20 (VCC), U6.16 (VCC), U7.24 (VCC), U9.20 (VCC); also elsewhere on the board
VDD: NT3.2, U3.25 (VDD), U8.7 (VDD)
VSS: NT4.2, U3.40 (VSS), U8.1 (VSS)
ZERO: U3.36 (~MC), U4.20 (~OE), U5.1 (OE), U6.5 (E2), U7.18 (~E), U8.22 (TEST), U9.11 (LE); also elsewhere on the board
bD0: U2.3 (D0); also elsewhere on the board
bD1: U2.4 (D1); also elsewhere on the board
bD2: U2.7 (D2); also elsewhere on the board
bD3: U2.8 (D3); also elsewhere on the board
bD4: U2.13 (D4); also elsewhere on the board
bD5: U2.14 (D5); also elsewhere on the board
bD6: U2.17 (D6); also elsewhere on the board
bD7: U2.18 (D7); also elsewhere on the board
~A15: U6.6 (E3); also elsewhere on the board
~CS_TTS: U3.12 (~INT3); also elsewhere on the board
~bRESET: U3.14 (~RESET), U8.2 (~RESET), U8.25 (~SBY_RESET); also elsewhere on the board

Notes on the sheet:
SW2 NOTE: SET CTS256A-AL2 INPUT OPTIONS 1-2=OFF (LOW) PARALLEL INPUT 3-4=OFF (LOW) PARALLEL INPUT 5-6=OFF (LOW) PARALLEL INPUT 7-8=ON (HIGH) SELECTABLE SERIAL PARAMETERS 9-10=ON (HIGH) EXTERNAL RAM BUFFER 11-12=OFF (LOW) CARRIAGE RETURN ONLY DELIMITER
SW3 NOTE: SET CTS256A-AL2 UART PARAMETERS (SEE UART TABLE 2 IN DATASHEET) 1-2=ON (HIGH) 1 STOP BIT 3-4=ON (HIGH) COMMUNICATION MODE 5-6=OFF (LOW) EVEN PARITY 7-8=ON (HIGH) NO PARITY 9-10=OFF (LOW) 8 DATA BITS 11-12=OFF (LOW) 8 DATA BITS 13-14=ON (HIGH) ASYNCHRONOUS COMMUNICATION 15-16=ON (HIGH) INT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
SET CTS256A-AL2 INPUT OPTIONS
SET CTS256A-AL2 UART PARAMETERS
GND ~{RTS} VCC RXD TXD ~{CTS}
UART PARAMETERS
EXPANDED INPUT BUFFER
PARALLEL PORT
PARALLEL DATA STROBE ACTIVE HIGH
EXTERNAL EPROM EXCEPTION WORD AND/OR USER DATA

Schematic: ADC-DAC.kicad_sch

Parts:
C28, C29, C55, C59, C60, C61: 0.1u; C_Disc_D5.0mm_W2.5mm_P5.00mm
C30: 47u; CP_Radial_D5.0mm_P2.50mm
C48, C58: 0.22u; C_Disc_D5.0mm_W2.5mm_P5.00mm
C49, C57: 100u; CP_Radial_D5.0mm_P2.50mm
C54: 3.9p; C_Disc_D5.0mm_W2.5mm_P5.00mm
C56: 0.01u; C_Disc_D5.0mm_W2.5mm_P5.00mm
D3: 1N4007; D_DO-41_SOD81_P10.16mm_Horizontal
J9: Microphone; Jack_3.5mm_PJ320E_Horizontal
J10: INTERRUPT; PinHeader_2x08_P2.54mm_Vertical
R9, R10, R11: 1000; R_Axial_DIN0207_L6.3mm_D2.5mm_P7.62mm_Horizontal
R12, R13, R14: 10K; R_Axial_DIN0207_L6.3mm_D2.5mm_P7.62mm_Horizontal
R15: 1; R_Axial_DIN0207_L6.3mm_D2.5mm_P7.62mm_Horizontal
R16, R17, R18, R19: 4700; R_Axial_DIN0207_L6.3mm_D2.5mm_P7.62mm_Horizontal
R20: 2200; R_Axial_DIN0207_L6.3mm_D2.5mm_P7.62mm_Horizontal
RV1: 500K; Potentiometer_Bourns_3386P_Vertical
U11, U15: LM741; DIP-8_W7.62mm_Socket
U12: 74LS06; DIP-14_W7.62mm_Socket
U13: 74LS273; DIP-20_W7.62mm_Socket
U14: DAC0800; DIP-16_W7.62mm_Socket
U16: ADC0820; DIP-20_W7.62mm_Socket

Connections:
+12V: C59.1, D3.2 (A), R16.2, U14.13 (V+), U15.7 (V+); also elsewhere on the board
-12V: C56.2, C61.1, U14.3 (V-), U15.4 (V-); also elsewhere on the board
/ADC-DAC/LSB: U13.19 (Q7), U14.12 (B7)
/ADC-DAC/MSB: U13.2 (Q0), U14.5 (B0)
/ADC-DAC/VIN+: C60.1, R15.1, U16.1 (VIN)
/ADC-DAC/VPRE: C55.2, C57.1, D3.1 (K), R9.1, R12.1, U11.7 (V+)
/ADC-DAC/~INTR: U12.1, U16.9 (~INTR)
AUDIO_DAC: R19.2, U15.6; also elsewhere on the board
GND: C28.1, C29.1, C30.2, C49.2, C55.1, C57.2, C59.2, C60.2, C61.2, J9.S, R13.2, R17.2, R18.2, U11.4 (V-), U13.10 (GND), U14.1 (VLC), U16.10 (GND), U16.11 (VREF-); also elsewhere on the board
unnamed: C48.1, R11.2
unnamed: C48.2, J9.T, R10.2
unnamed: C49.1, R9.2, R10.1
unnamed: C54.1, R14.2, RV1.1, RV1.2
unnamed: C54.2, R11.1, RV1.3, U11.2 (-)
unnamed: C56.1, U14.16 (CMP)
unnamed: C58.1, R15.2
unnamed: C58.2, R14.1, U11.6
unnamed: J10.1, J10.3, J10.5, J10.7, J10.9, J10.11, J10.13, J10.15, U12.4
unnamed: R12.2, R13.1, U11.3 (+)
unnamed: R16.1, U14.14 (R+)
unnamed: R17.1, U14.15 (R-)
unnamed: R18.1, U14.4 (I-), U15.2 (-)
unnamed: R19.1, U14.2 (I+), U15.3 (+)
unnamed: R20.2, U12.2, U12.3
unnamed: U13.5 (Q1), U14.6 (B1)
unnamed: U13.6 (Q2), U14.7 (B2)
unnamed: U13.9 (Q3), U14.8 (B3)
unnamed: U13.12 (Q4), U14.9 (B4)
unnamed: U13.15 (Q5), U14.10 (B5)
unnamed: U13.16 (Q6), U14.11 (B6)
ONE: U16.7 (MODE); also elsewhere on the board
VCC: C28.2, C29.2, C30.1, R20.1, U13.20 (VCC), U16.12 (VREF+), U16.20 (VCC); also elsewhere on the board
bD0: U13.18 (D7), U16.2 (DB0); also elsewhere on the board
bD1: U13.17 (D6), U16.3 (DB1); also elsewhere on the board
bD2: U13.14 (D5), U16.4 (DB2); also elsewhere on the board
bD3: U13.13 (D4), U16.5 (DB3); also elsewhere on the board
bD4: U13.8 (D3), U16.14 (DB4); also elsewhere on the board
bD5: U13.7 (D2), U16.15 (DB5); also elsewhere on the board
bD6: U13.4 (D1), U16.16 (DB6); also elsewhere on the board
bD7: U13.3 (D0), U16.17 (DB7); also elsewhere on the board
~CS_ADC_WR: U16.6 (~WR/RDY); also elsewhere on the board
~CS_ADC: U16.13 (~CS); also elsewhere on the board
~CS_DAC_WR: U13.11 (Cp); also elsewhere on the board
~EIRQ0: J10.2; also elsewhere on the board
~EIRQ1: J10.4; also elsewhere on the board
~EIRQ2: J10.6; also elsewhere on the board
~EIRQ3: J10.8; also elsewhere on the board
~EIRQ4: J10.10; also elsewhere on the board
~EIRQ5: J10.12; also elsewhere on the board
~EIRQ6: J10.14; also elsewhere on the board
~EIRQ7: J10.16; also elsewhere on the board
~bRD: U16.8 (~RD); also elsewhere on the board
~bRESET: U13.1 (~Mr); also elsewhere on the board

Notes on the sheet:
DIGITAL TO ANALOG CONVERTER
NOTE: INTERRUPT RELIES ON 4700 OHM PULL UP RESISTOR ON PROCESSOR BOARD
ANALOG TO DIGITAL CONVERTER
MICROPHONE PRE-AMPLIFIER
NOTE: MICROPHONE JACK 3.5 mm Audio Jack Connector PCB Product Name: WQP-PJ320E WQP-PJ320E is a 3.5mm audio jack, DIP type, right angle.

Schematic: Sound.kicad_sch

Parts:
R24, R25: 2200; R_Axial_DIN0207_L6.3mm_D2.5mm_P7.62mm_Horizontal
U12: 74LS06; DIP-14_W7.62mm_Socket
U23, U24: SN76489; DIP-16_W7.62mm_Socket
X1: 3.5795 MHz; DIP-8_W7.62mm_Socket

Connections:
/Sound/SN_CLK: U23.14 (CLOCK), U24.14 (CLOCK), X1.5
/Sound/~SN_WAIT: R24.2, U12.5, U23.4 (READY), U24.4 (READY)
AUDIO_SNL: U23.7 (AUDIO); also elsewhere on the board
AUDIO_SNR: U24.7 (AUDIO); also elsewhere on the board
GND: U23.8 (GND), U24.8 (GND), X1.4; also elsewhere on the board
unnamed: R25.2, U12.6, U12.9
VCC: R24.1, R25.1, U23.16 (VCC), U24.16 (VCC), X1.1, X1.8; also elsewhere on the board
bD0: U23.10 (D0), U24.10 (D0); also elsewhere on the board
bD1: U23.11 (D1), U24.11 (D1); also elsewhere on the board
bD2: U23.12 (D2), U24.12 (D2); also elsewhere on the board
bD3: U23.13 (D3), U24.13 (D3); also elsewhere on the board
bD4: U23.15 (D4), U24.15 (D4); also elsewhere on the board
bD5: U23.1 (D5), U24.1 (D5); also elsewhere on the board
bD6: U23.2 (D6), U24.2 (D6); also elsewhere on the board
bD7: U23.3 (D7), U24.3 (D7); also elsewhere on the board
~CS_SN1: U23.6 (~OE); also elsewhere on the board
~CS_SN2: U24.6 (~OE); also elsewhere on the board
~WAIT: U12.8; also elsewhere on the board
~bWR: U23.5 (~WE), U24.5 (~WE); also elsewhere on the board

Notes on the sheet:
SN76489 DCSG (PSG) WRITE ONLY
